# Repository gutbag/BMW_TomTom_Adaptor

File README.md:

# BMW Nav Mount To TomTom Adaptor

## Description
These are the design files for an adaptor to allow TomTom sat navs to be mounted on, and powered by, a BMW Nav Mount. The project involves 3D printed components, two PCBs, a 12V/5V converter module and some custom-moulded silicone rubber seals for waterproofing.

## Mechanical Components
The mechanical components are designed using FreeCAD. The model contains the parts for the adaptor and some support components such as the mould and lid for the silicone seals.

### AdaptorBase
Fits to the BMW Nav Mount using the standard locking mechanism. Contains a PCB that connnects to the BMW's 12V supply pins, a magnet to turn on the 12V and two silicone seals to prevent water ingress.

### TomTomMount
Fits into the back of the TomTom. Provides a mechanism for a locator block with locking 'key' so that the TomTom with the mount can be removed from the bike without the rest of the relatively bulky adaptor.

### TomTomLocatorBlock
Fits into the TomTomMount and can be locked to it. Contains a PCB with two pogo pins that supply 5V to the TomTom. A small silicone rubber seal surrounds the pogo pins and should be glued in place.

### InternalSupport
Fits between the TomTomLocatorBlock and the AdaptorBase to keep the TomTom PCB and the BMW PCB in place.

## Electronics
The TomTom and BMW PCBs are designed in KiCad. They are made as a single PCB that needs to be separated before assembly. A 12V/5V buck converter module sits between them.

### BMW PCB
Picks up the 0V and 12V pogo pins from the Nav Mount and provides pads for the wires connecting to the buck converter module. A surface mount LED and current limiting resistor can be fitted to confirm that the 12V is present. This is useful during development but may not be in the final adaptor if the material used for the body is opaque. The PCB holds a silicone seal in place.

It is recommended that the BMW PCB's rear pads are gold plated to improve their lifespan and maintain a low resistance connection. It would also be worth increasing the number of vias on the 0V and 12V tracks.

### TomTom PCB
Requires two pogo pins to be mounted and soldered, plus two wires to the buck converter.

### Buck Converter
Converts the BMW 12V to the 5V required by the TomTom. The module used allows an LED with resistors to be fitted across the output to confirm that the 5V is present.

### Internal Wiring
The wiring between the PCBs and the buck converter needs to be short and follow the openings designed for it, particularly in the InternalSupport component.

## Silicone Seals
The FreeCAD model includes a mould for the three silicone seals. These can be made using two-part silicone resin. A mould lid can be used to control the thickness of the seals, although the innermost part of the BMW PCB seal is open to minimise bubbles.

# Bought-In Parts
TomTom PCB pogo pins: aliexpress. 2mm diameter, 14mm length.
Buck converter: kunkune.co.uk 'Mini Step Down Buck Converter 5-30V, 5V output'

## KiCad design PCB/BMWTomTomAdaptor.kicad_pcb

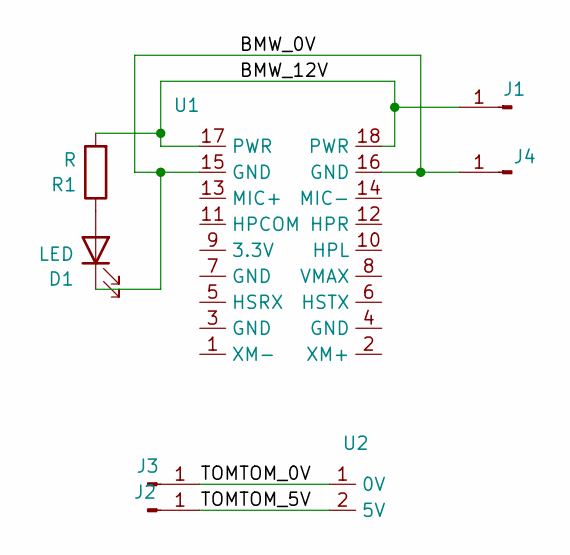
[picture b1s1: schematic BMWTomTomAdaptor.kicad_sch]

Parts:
D1: LED; LED_1206_3216Metric_Pad1.42x1.75mm_HandSolder
J1, J2, J3, J4: Conn_01x01_Pin; Wire Solder Pad
R1: R; R_0805_2012Metric_Pad1.20x1.40mm_HandSolder
U1: BMWNavConnector
U2: TomTomPogoPins

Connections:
/BMW_0V: D1.1 (K), J4.1, U1.15 (GND), U1.16 (GND)
/BMW_12V: J1.1, R1.2, U1.17 (PWR), U1.18 (PWR)
/TOMTOM_0V: J3.1, U2.1 (0V)
/TOMTOM_5V: J2.1, U2.2 (5V)
unnamed: D1.2 (A), R1.1

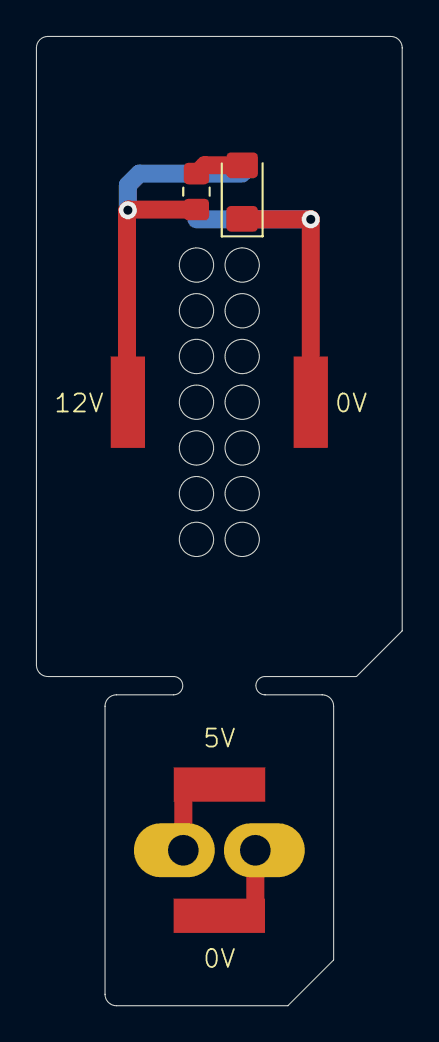
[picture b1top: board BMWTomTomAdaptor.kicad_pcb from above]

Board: 2 copper layers, 20.3 x 53.8 mm, 8 parts (1 on the bottom side), 5 nets.

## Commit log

2025-09-18 Slightly updated first version
2025-09-18 second print
2025-09-18 third print
2025-09-18 fourth print
2025-09-21 print 5 with separate dummy PCB
2025-09-22 changes after print 5
2025-09-23 TomTom plate print 1
2025-09-23 TomTom plate print 2
2025-09-23 TomTom plate print 3
2025-09-25 first print of TomTom mount with locator insert
2025-09-26 2nd TomTom locator print, 6th adaptor base with magnet
2025-09-30 first print of locator with rear plate
2025-10-01 First commit of PCB design(s)
2025-10-03 Added InternalSupport
2025-10-07 Print 7 Oct 25 - added internal support etc.
2025-10-08 8 Oct 25 print - everything fits but no PCBs yet
2025-10-13 Added passive adaptor
2025-10-20 Printed 20 Oct 2025
2025-10-20 2nd print 20 Oct 2025
2025-10-22 Made wider to allow for waterproofing
2025-10-22 Added waterproofing slots - provisional
2025-10-22 Updated waterproofing for 2mm sq beading
2025-10-25 Added TomTomCover
2025-10-27 Added simple top lock - not printed
2025-10-27 Added bottom lock features and 'key'
2025-10-27 Small refinements of lock
2025-10-28 Printed 28Oct25
2025-10-29 Print 29Oct25 - mostly lock changes
2025-10-29 Make tether eye stronger
2025-11-01 Reduced depth of waterproof channel on TTLocatorBlock
2025-11-03 Changed lock to vertical
2025-11-04 Added silicone helper and vert lock key
2025-11-27 Added silicone mould
2025-11-27 added readme
2025-12-04 Added silicone mould lid and draining recesses
2025-12-09 Small changes after 5 Dec 2025 print
2025-12-16 Flange inside adaptor and mould lid opening to try to prevent bubbles
2025-12-16 Mould lid with opening
2025-12-17 Fix BMW seal mould inner edge height
2025-12-21 Minor tidying and step export for print 20Dec25
2025-12-21 Fixed TTLocatorBlock flip
2025-12-21 Add doc
2025-12-21 photo
2025-12-21 updated doc
2025-12-26 Deeper BMW seal and step file for vertical lock
